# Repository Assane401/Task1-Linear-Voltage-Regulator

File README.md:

# Task 1 – Linear Voltage Regulator (5V)

**Author:** Assane DIENG  
**Date:** March 2026  
**Context:** EUtech Engineers – Electrical Engineering Apprenticeship

## 🎯 Objective

Design and test a 5V regulated power supply using a linear voltage regulator (L7805CV).

## 📁 Repository Structure
Task1-Linear-Voltage-Regulator/
├── KiCad/               # Schematic & PCB layout files
├── Gerbers/             # Gerber files for manufacturing
├── LTSpice/             # Simulation files
├── BOM/                 # Bill of Materials
├── Report/              # Final design report (PDF)
└── Screenshots/         # Captures of schematic, PCB, simulation

## ⚙️ Components

| Component | Reference | Value |
|-----------|-----------|-------|
| Voltage Regulator | L7805CV | 5V 
| Input capacitor | C1 | 330 nF |
| Output capacitor | C2 | 100 nF |
| LED indicator | D1 | Green |
| Current limiting resistor | R1 | 

## 🔧 Tools Used

- **KiCad** – Schematic & PCB design
- **LTSpice** – Circuit simulation
- **Git / GitHub** – Version control

## 📄 Report

The full design report is available. It covers:
- Working principle of the L7805CV
- Design choices (capacitors, thermal analysis, trace width)
- Simulation results
- PCB layout decisions

## 📬 Contact
For any questions or remarks, feel free to reach out: dieng.assane98@yahoo.com

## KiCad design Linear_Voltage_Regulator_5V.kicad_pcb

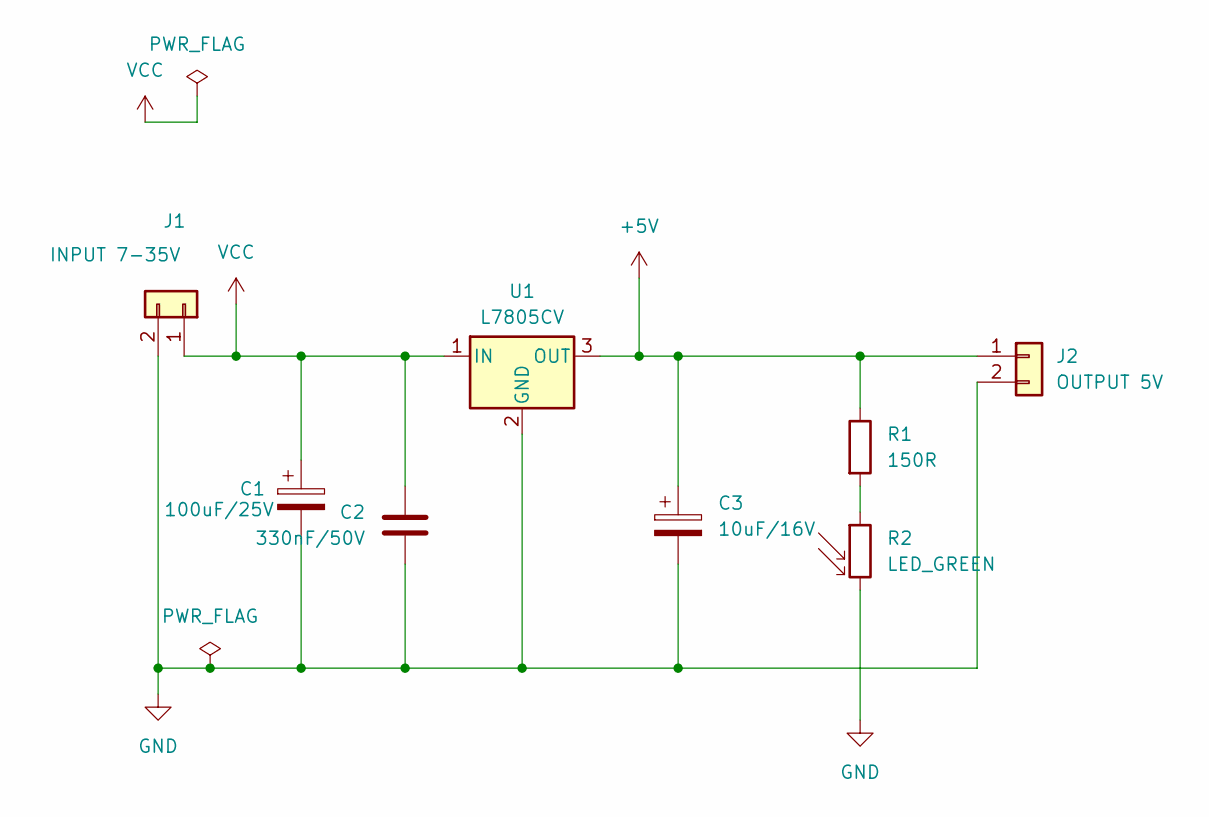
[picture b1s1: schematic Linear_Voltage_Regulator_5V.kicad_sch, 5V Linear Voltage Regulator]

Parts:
C1: 100uF/25V; CP_Radial_D8.0mm_P3.50mm
C2: 330nF/50V; C_Disc_D5.0mm_W2.5mm_P5.00mm
C3: 10uF/16V; CP_Radial_D5.0mm_P2.50mm
J1: INPUT 7-35V; PinHeader_1x02_P2.54mm_Vertical
J2: OUTPUT 5V; PinHeader_1x02_P2.54mm_Vertical
R1: 150R; R_Axial_DIN0207_L6.3mm_D2.5mm_P10.16mm_Horizontal
R2: LED_GREEN; LED_D3.0mm
U1: L7805CV; TO-220-3_Vertical

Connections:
+5V: C3.1, J2.1, R1.1, U1.3 (OUT)
GND: C1.2, C2.2, C3.2, J1.2, J2.2, R2.2, U1.2 (GND)
unnamed: R1.2, R2.1
VCC: C1.1, C2.1, J1.1, U1.1 (IN)

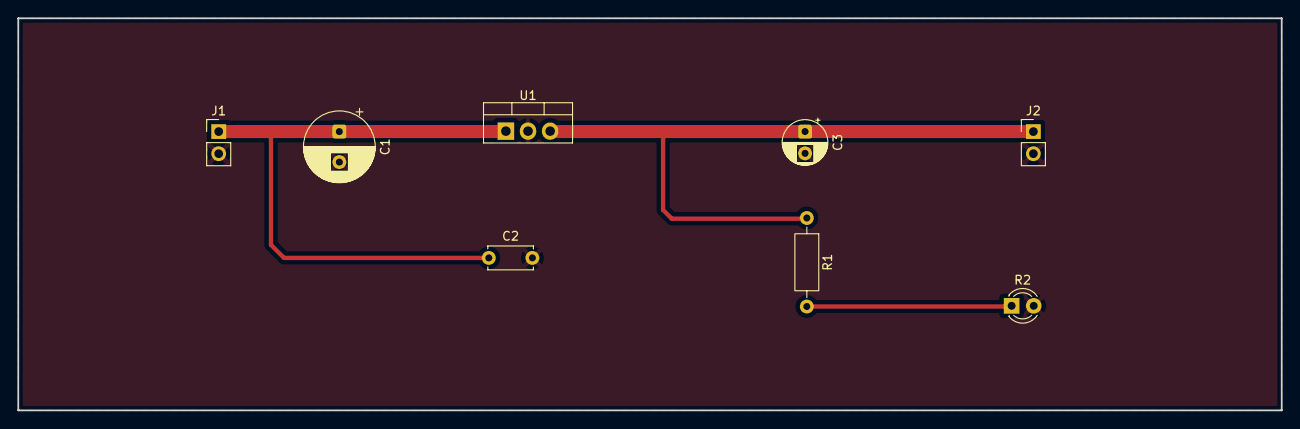
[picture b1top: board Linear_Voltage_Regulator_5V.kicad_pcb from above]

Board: 2 copper layers, 145.0 x 45.0 mm, 8 parts (0 on the bottom side), 4 nets.

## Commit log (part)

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2026-03-03 Task1:L7805CV 5V complete-schematic+layout+gerbers
2026-03-15 Create Task1
2026-03-18 Task1: ajout rapport + BOM + nettoyage fichiers temporaires
